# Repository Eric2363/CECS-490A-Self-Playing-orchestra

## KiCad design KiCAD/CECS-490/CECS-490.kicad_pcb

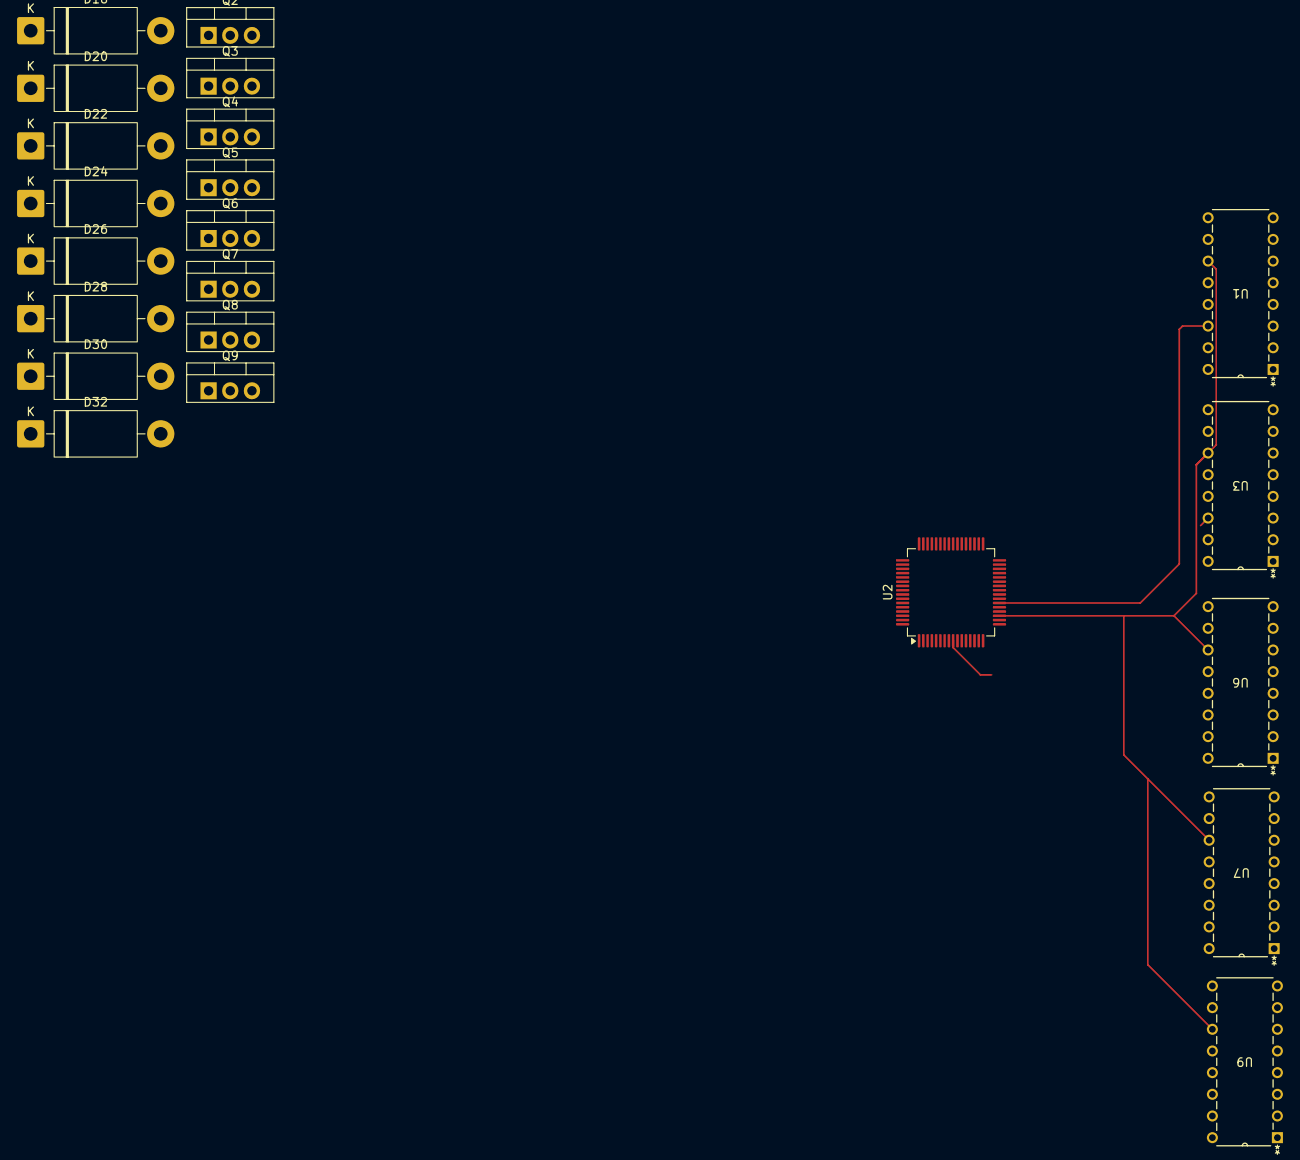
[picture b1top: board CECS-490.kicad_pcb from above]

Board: 2 copper layers, 22 parts (0 on the bottom side), 19 nets.

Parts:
D16, D20, D22, D24, D26, D28, D30, D32: 1N5408; D_DO-201AD_P15.24mm_Horizontal
Q2, Q3, Q4, Q5, Q6, Q7, Q8, Q9: IRLZ44N; TO-220-3_Vertical
U1, U3, U6, U7, U9: SN74HC595N; N16
U2: TM4C1230H6PM; LQFP-64_10x10mm_P0.5mm

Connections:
+3.3V: U1.10 (*SRCLR), U1.16 (VCC), U2.2 (VDDA), U2.11 (VDD), U2.26 (VDD), U2.37 (PG0/T4CCP0/I2C3SCL), U2.42 (VDD), U2.54 (VDD), U3.10 (*SRCLR), U3.16 (VCC), U6.10 (*SRCLR), U6.16 (VCC), U7.10 (*SRCLR), U7.16 (VCC), U9.10 (*SRCLR), U9.16 (VCC)
+24V: D16.1 (K), D20.1 (K), D22.1 (K), D24.1 (K), D26.1 (K), D28.1 (K), D30.1 (K), D32.1 (K)
A2: U1.11 (SRCLK), U2.19 (SSI0CLK/PA2), U3.11 (SRCLK), U6.11 (SRCLK), U7.11 (SRCLK), U9.11 (SRCLK)
A5: U1.14 (SER), U2.22 (SSI0TX/PA5)
E0: U1.12 (RCLK), U2.9 (PE0/AIN3/U7RX), U3.12 (RCLK), U6.12 (RCLK), U7.12 (RCLK), U9.12 (RCLK)
GND: Q2.3 (S), Q3.3 (S), Q4.3 (S), Q5.3 (S), Q6.3 (S), Q7.3 (S), Q8.3 (S), Q9.3 (S), U1.8 (GND), U1.13 (*OE), U2.3 (GNDA), U2.12 (GND), U2.27 (GND), U2.39 (GND), U2.55 (GND), U3.8 (GND), U3.13 (*OE), U6.8 (GND), U6.13 (*OE), U7.8 (GND), U7.13 (*OE), U9.8 (GND), U9.13 (*OE)
unnamed: U2.25 (VDDC), U2.56 (VDDC)
unnamed: D16.2 (A), Q2.2 (D)
unnamed: D20.2 (A), Q3.2 (D)
unnamed: D22.2 (A), Q4.2 (D)
unnamed: D24.2 (A), Q5.2 (D)
unnamed: D26.2 (A), Q6.2 (D)
unnamed: D28.2 (A), Q7.2 (D)
unnamed: D30.2 (A), Q8.2 (D)
unnamed: D32.2 (A), Q9.2 (D)
unnamed: U1.9 (QH'), U3.14 (SER)
unnamed: U3.9 (QH'), U6.14 (SER)
unnamed: U6.9 (QH'), U7.14 (SER)
unnamed: U7.9 (QH'), U9.14 (SER)

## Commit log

2026-03-04 Add .gitignore for various build and editor files
2026-04-22 Organized files
2026-04-26 Added MOSFET driver
2026-04-27 Added schematic with MOSFET driver.
2026-04-29 Added KiCAD project
2026-05-04 Added support circuit for MCU
